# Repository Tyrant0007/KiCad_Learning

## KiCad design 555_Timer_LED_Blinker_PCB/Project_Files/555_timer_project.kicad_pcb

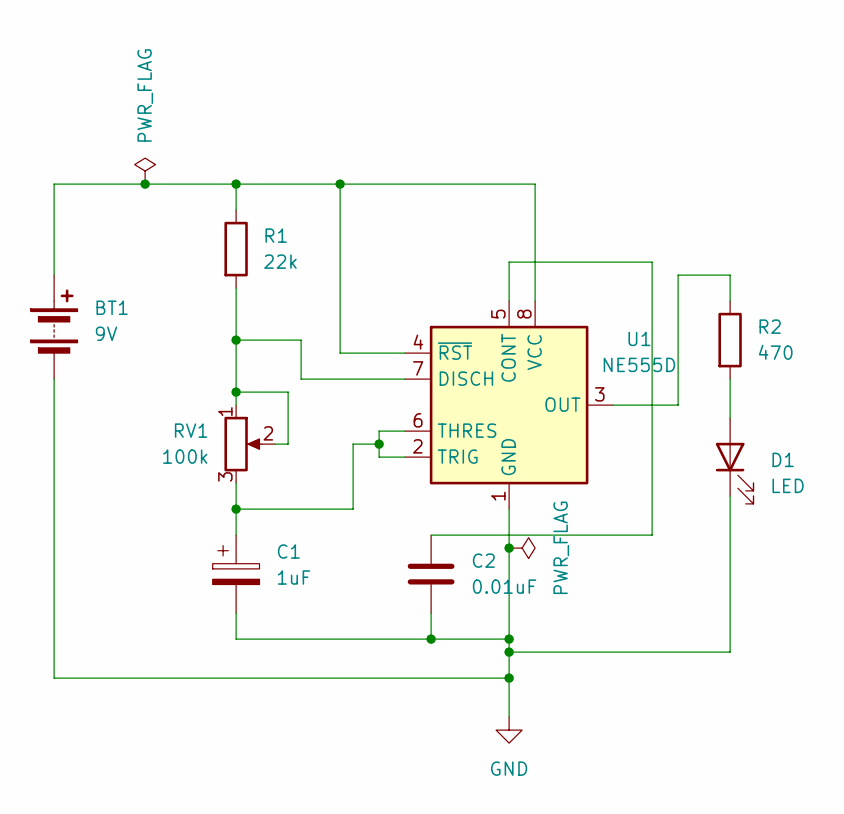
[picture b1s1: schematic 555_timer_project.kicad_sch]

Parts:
BT1: 9V; PinHeader_1x02_P2.54mm_Horizontal
C1: 1uF; C_Radial_D4.0mm_H5.0mm_P1.50mm
C2: 0.01uF; C_Disc_D3.0mm_W1.6mm_P2.50mm
D1: LED; LED_D5.0mm
R1: 22k; R_Axial_DIN0204_L3.6mm_D1.6mm_P1.90mm_Vertical
R2: 470; R_Axial_DIN0204_L3.6mm_D1.6mm_P1.90mm_Vertical
RV1: 100k; Potentiometer_Bourns_3296W_Vertical
U1: NE555D; SOIC-8_3.9x4.9mm_P1.27mm

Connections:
GND: BT1.2 (-), C1.2, C2.2, D1.1 (K), U1.1 (GND)
unnamed: BT1.1 (+), R1.1, U1.4 (~RST), U1.8 (VCC)
unnamed: D1.2 (A), R2.2
unnamed: C2.1, U1.5 (CONT)
unnamed: R1.2, RV1.1, RV1.2, U1.7 (DISCH)
unnamed: R2.1, U1.3 (OUT)
unnamed: C1.1, RV1.3, U1.2 (TRIG), U1.6 (THRES)

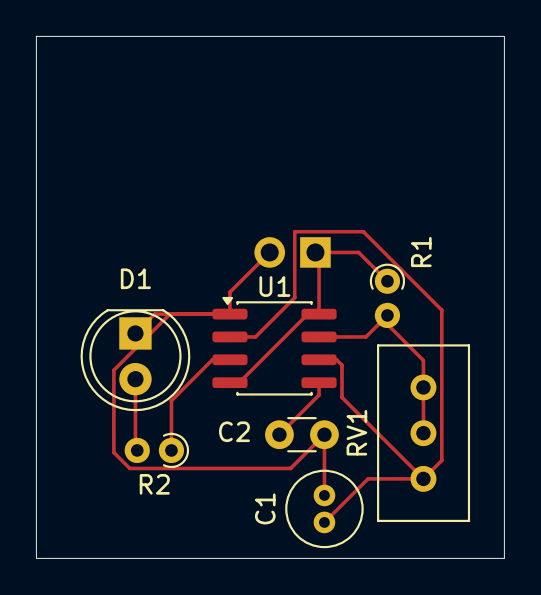
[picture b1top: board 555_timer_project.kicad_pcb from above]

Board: 2 copper layers, 26.0 x 29.0 mm, 8 parts (1 on the bottom side), 7 nets.

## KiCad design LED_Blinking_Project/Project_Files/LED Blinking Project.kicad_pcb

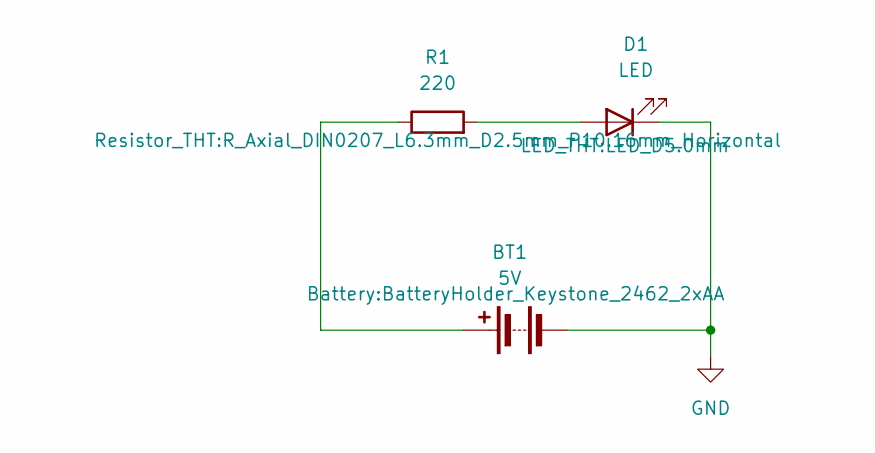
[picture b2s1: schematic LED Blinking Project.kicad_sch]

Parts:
BT1: 5V; BatteryHolder_Keystone_2462_2xAA
D1: LED; LED_D5.0mm
R1: 220; R_Axial_DIN0207_L6.3mm_D2.5mm_P10.16mm_Horizontal

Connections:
GND: BT1.2 (-), D1.1 (K)
unnamed: BT1.1 (+), R1.1
unnamed: D1.2 (A), R1.2

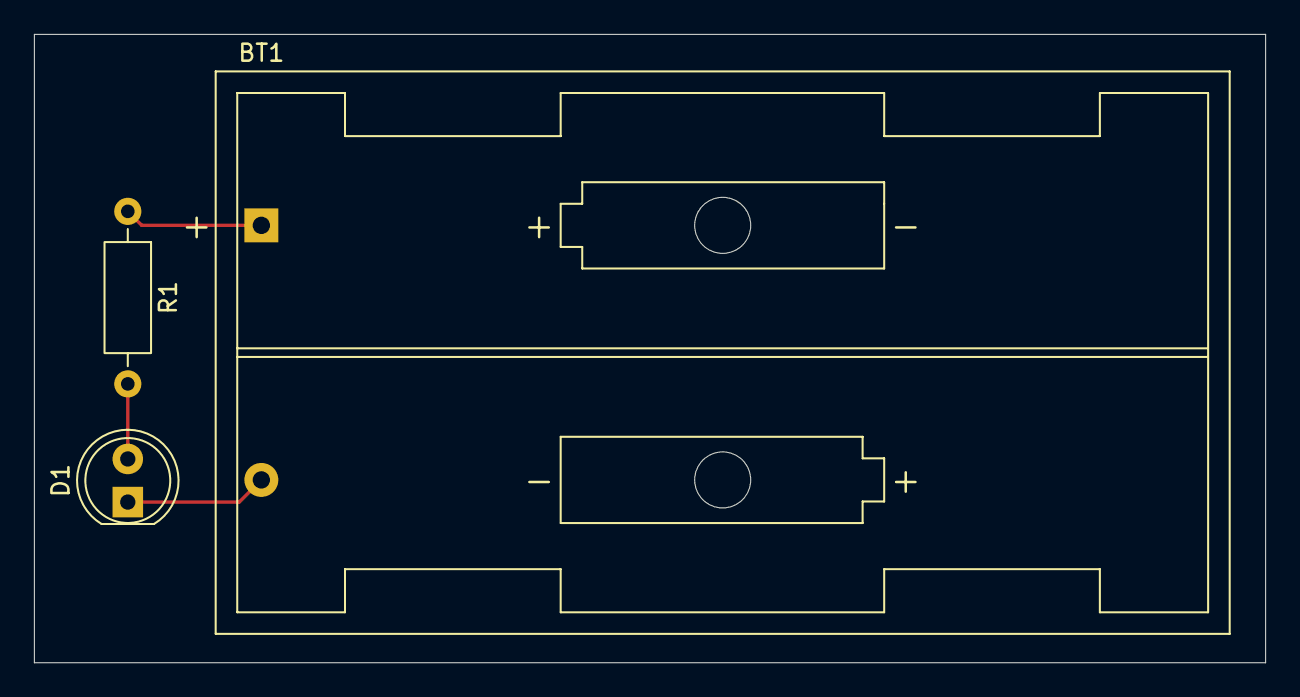
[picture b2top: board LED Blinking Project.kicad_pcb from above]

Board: 2 copper layers, 72.5 x 37.0 mm, 3 parts (0 on the bottom side), 3 nets.

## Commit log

2026-05-23 Add files via upload
    Initial LED PCB project upload
2026-05-25 Added README for LED blinking project
2026-05-25 Create Project_Files
